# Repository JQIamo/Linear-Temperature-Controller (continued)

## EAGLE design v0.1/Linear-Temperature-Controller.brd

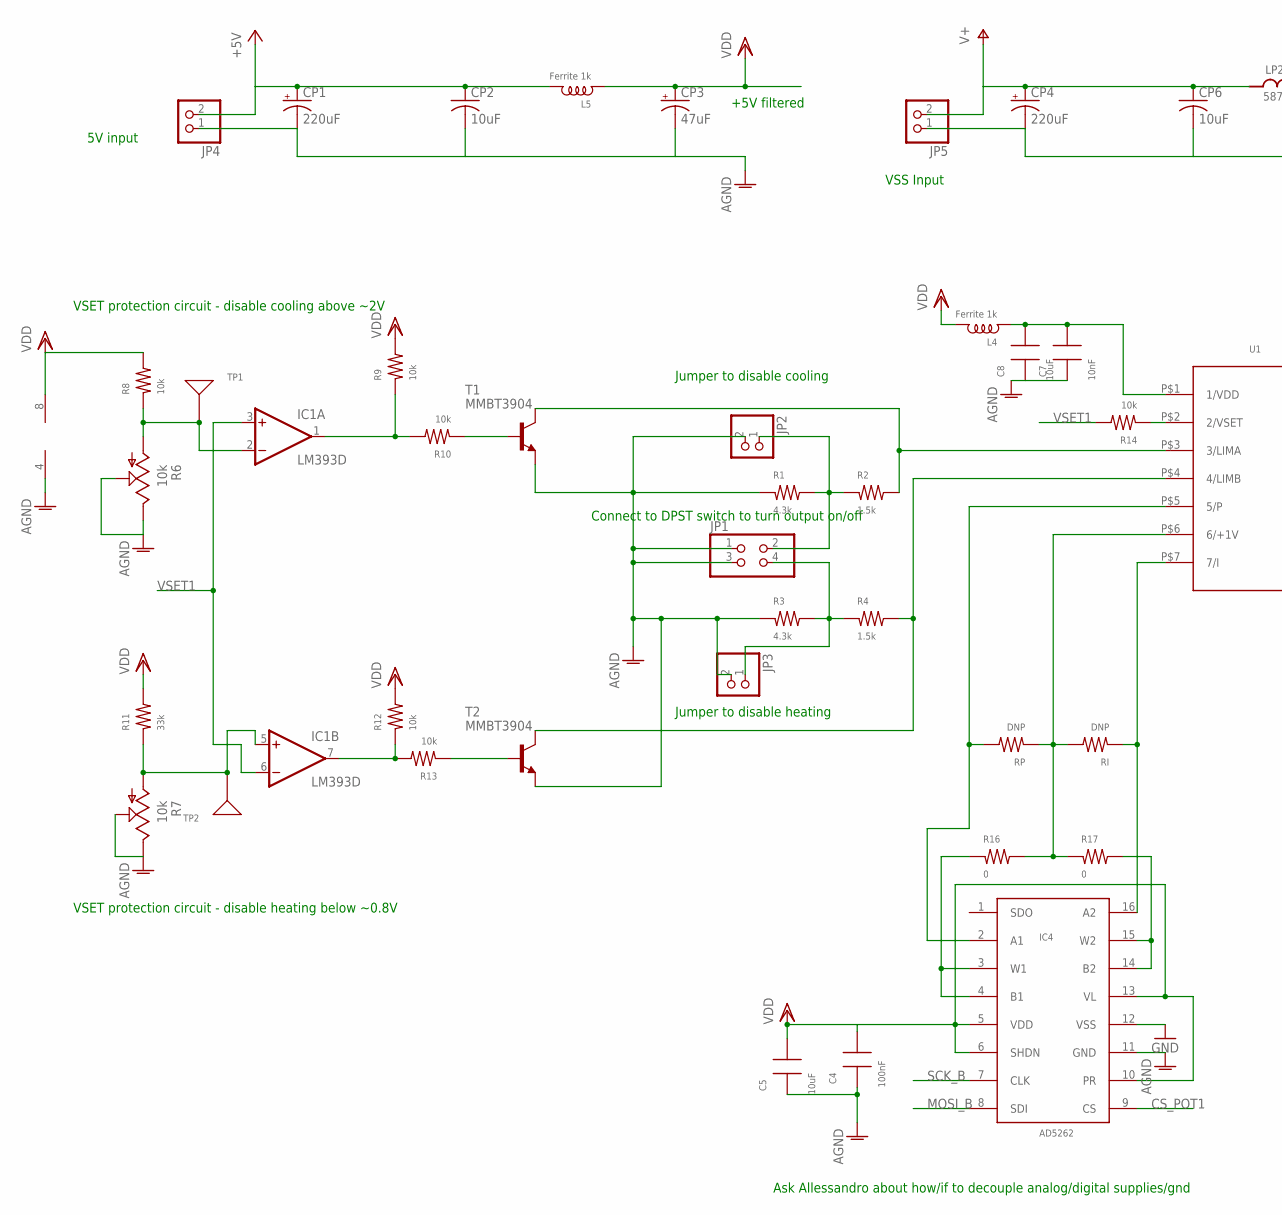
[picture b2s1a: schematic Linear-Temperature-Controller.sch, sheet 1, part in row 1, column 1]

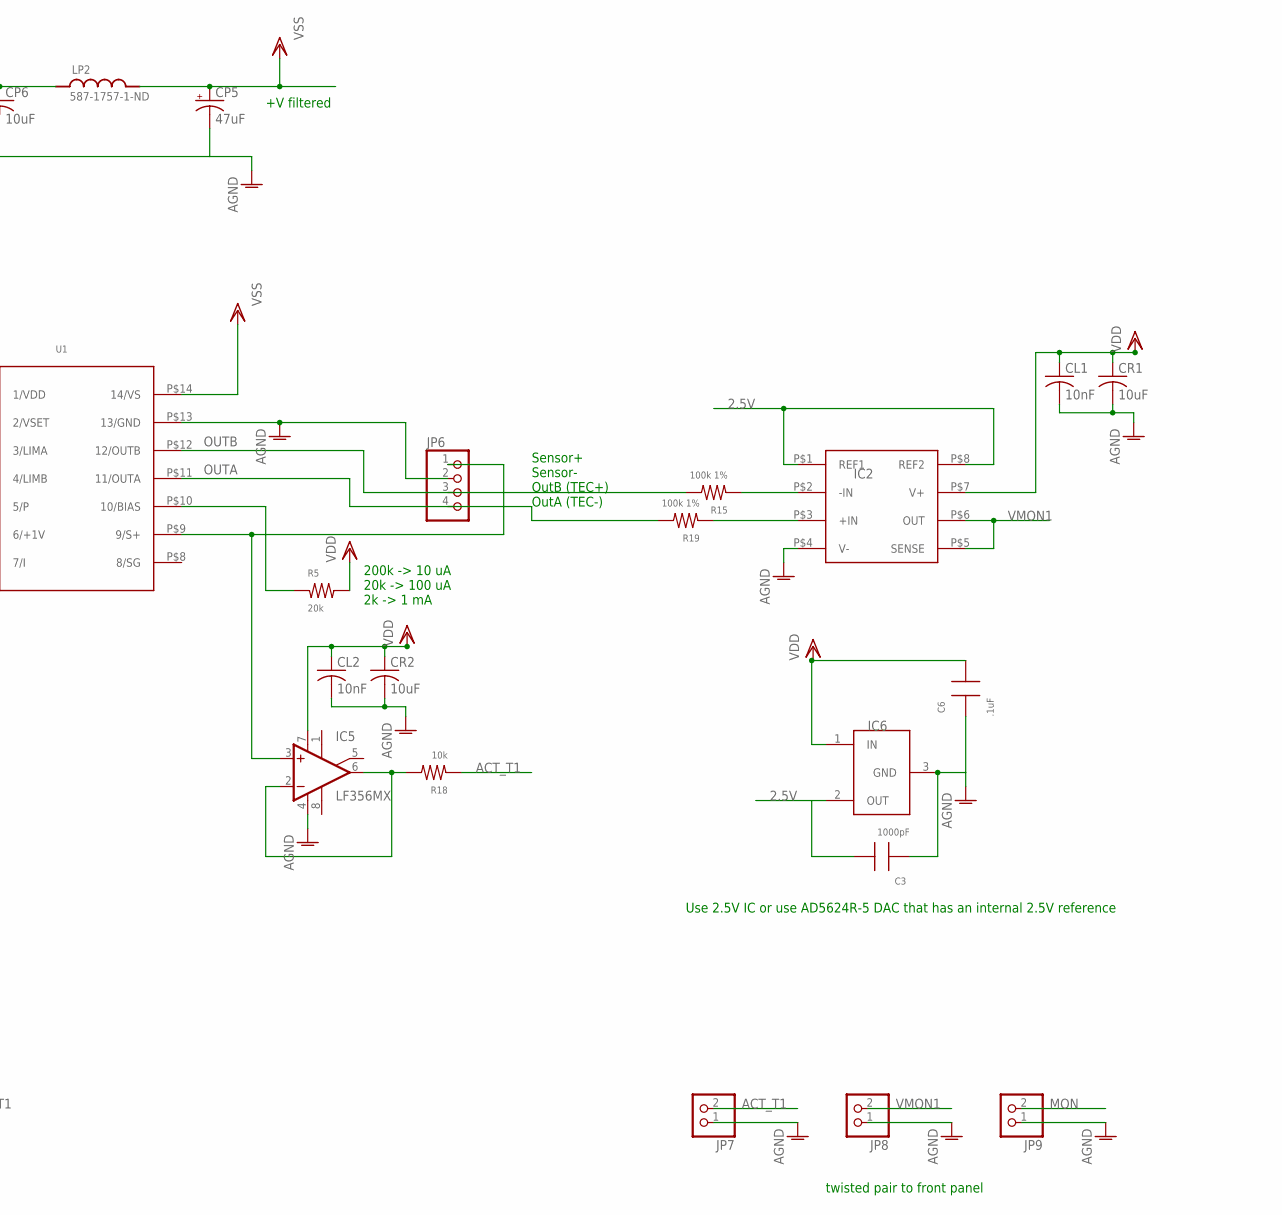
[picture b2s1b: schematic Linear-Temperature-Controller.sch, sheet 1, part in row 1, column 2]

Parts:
C3: 1000pF; 0805
C4: 100nF; 0805
C5, C8: 10uF; 0805
C6: .1uF; 0805
C7: 10nF; 0805
CL1, CL2: 10nF; C0805
CP1, CP4: 220uF; PANASONIC_F
CP2, CP6: 10uF; C0805K
CP3, CP5: 47uF; CT7343
CR1, CR2: 10uF; C0805
IC1: LM393D; SO08
IC2: INA159; VSSOP8
IC4: AD5262; TSSOP16
IC5: LF356MX; SO08
IC6: TS6001; SOT-23
JP1: PINHD-2X2; 2X02
JP2, JP3, JP4, JP5, JP7, JP8, JP9: PINHD-1X2; 1X02
JP6: PINHD-1X4; 1X04
L4, L5: Ferrite 1k; 0805
LP2: 587-1757-1-ND; L_FERRITE_1810
R1, R3: 4.3k; 0805
R2, R4: 1.5k; 0805
R5: 20k; 0805
R6, R7: 10k; 64XPOT
R8, R9, R10, R12, R13, R14, R18: 10k; 0805
R11: 33k; 0805
R15, R19: 100k 1%; 1206
R16, R17: 0; 0805
RI: DNP; 0805
RP: DNP; 0805
T1, T2: MMBT3904; SOT-23
TP1, TP2: TESTPT; 1206TESTPAD
U1: WTC3243; WTC3293

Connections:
2.5V: C3.2, IC2.P$1 (REF1), IC2.P$8 (REF2), IC6.2 (OUT); also elsewhere on the board
+5V: CP1.+, CP2.1, JP4.2, L5.2
ACT_T1: JP7.2, R18.1; also elsewhere on the board
AGND: C3.1, C4.1, C5.1, C6.1, C7.1, C8.1, CL1.2, CL2.2, CP1.-, CP2.2, CP3.-, CP4.-, CP5.-, CP6.2, CR1.2, CR2.2, IC1.4 (V-), IC2.P$4 (V-), IC4.11 (GND), IC5.4 (V-), IC6.3 (GND), JP1.1, JP1.3, JP2.2, JP3.2, JP4.1, JP5.1, JP6.2, JP7.1, JP8.1, JP9.1, R1.1, R3.1, R6.P$2 (2), R6.P$3 (3), R7.P$2 (2), R7.P$3 (3), T1.2 (E), T2.2 (E), U1.P$13 (13/GND); also elsewhere on the board
CS_POT1: IC4.9 (CS); also elsewhere on the board
DGND: IC4.12 (VSS); also elsewhere on the board
MON: JP9.2; also elsewhere on the board
MOSI_B: IC4.8 (SDI); also elsewhere on the board
unnamed: R2.2, T1.3 (C), U1.P$3 (3/LIMA)
unnamed: JP1.2, JP2.1, R1.2, R2.1
unnamed: R4.2, T2.3 (C), U1.P$4 (4/LIMB)
unnamed: JP1.4, JP3.1, R3.2, R4.1
unnamed: R5.1, U1.P$10 (10/BIAS)
unnamed: IC1.2 (-IN), R6.P$1 (1), R8.1, TP1.P$1
unnamed: IC1.5 (+IN), R7.P$1 (1), R11.1, TP2.P$1
unnamed: IC1.7 (OUT), R12.1, R13.2
unnamed: IC1.1 (OUT), R9.1, R10.2
unnamed: R10.1, T1.1 (B)
unnamed: R13.1, T2.1 (B)
unnamed: R14.1, U1.P$2 (2/VSET)
unnamed: IC5.3 (+IN), JP6.1, U1.P$9 (9/S+)
unnamed: IC2.P$2 (-IN), R15.1
unnamed: IC4.2 (A1), RP.2, U1.P$5 (5/P)
unnamed: IC2.P$3 (+IN), R19.1
unnamed: R16.2, R17.1, RI.2, RP.1, U1.P$6 (6/+1V)
unnamed: IC4.3 (W1), IC4.4 (B1), R16.1
unnamed: IC4.16 (A2), RI.1, U1.P$7 (7/I)
unnamed: IC4.14 (B2), IC4.15 (W2), R17.2
unnamed: IC5.2 (-IN), IC5.6 (OUT), R18.2
unnamed: C7.2, C8.2, L4.1, U1.P$1 (1/VDD)
OUTA: JP6.4, R19.2, U1.P$11 (11/OUTA)
OUTB: JP6.3, R15.2, U1.P$12 (12/OUTB)
SCK_B: IC4.7 (CLK); also elsewhere on the board
V+: CP4.+, CP6.1, JP5.2, LP2.P$1 (1)
VDD: C4.2, C5.2, C6.2, CL1.1, CL2.1, CP3.+, CR1.1, CR2.1, IC1.8 (V+), IC2.P$7 (V+), IC4.5 (VDD), IC4.6 (SHDN), IC4.10 (PR), IC4.13 (VL), IC5.7 (V+), IC6.1 (IN), L4.2, L5.1, R5.2, R8.2, R9.2, R11.2, R12.2; also elsewhere on the board
VMON1: IC2.P$5 (SENSE), IC2.P$6 (OUT), JP8.2; also elsewhere on the board
VSET1: IC1.3 (+IN), IC1.6 (-IN), R14.2; also elsewhere on the board
VSS: CP5.+, LP2.P$2 (2), U1.P$14 (14/VS)

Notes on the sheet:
Jumper to disable heating
Jumper to disable cooling
Connect to DPST switch to turn output on/off
200k -> 10 uA 20k -> 100 uA 2k -> 1 mA
VSET protection circuit - disable heating below ~0.8V
VSET protection circuit - disable cooling above ~2V
+5V filtered
+V filtered
5V input
VSS Input
Sensor+ Sensor- OutB (TEC+) OutA (TEC-)
Ask Allessandro about how/if to decouple analog/digital supplies/gnd
twisted pair to front panel
Use 2.5V IC or use AD5624R-5 DAC that has an internal 2.5V reference

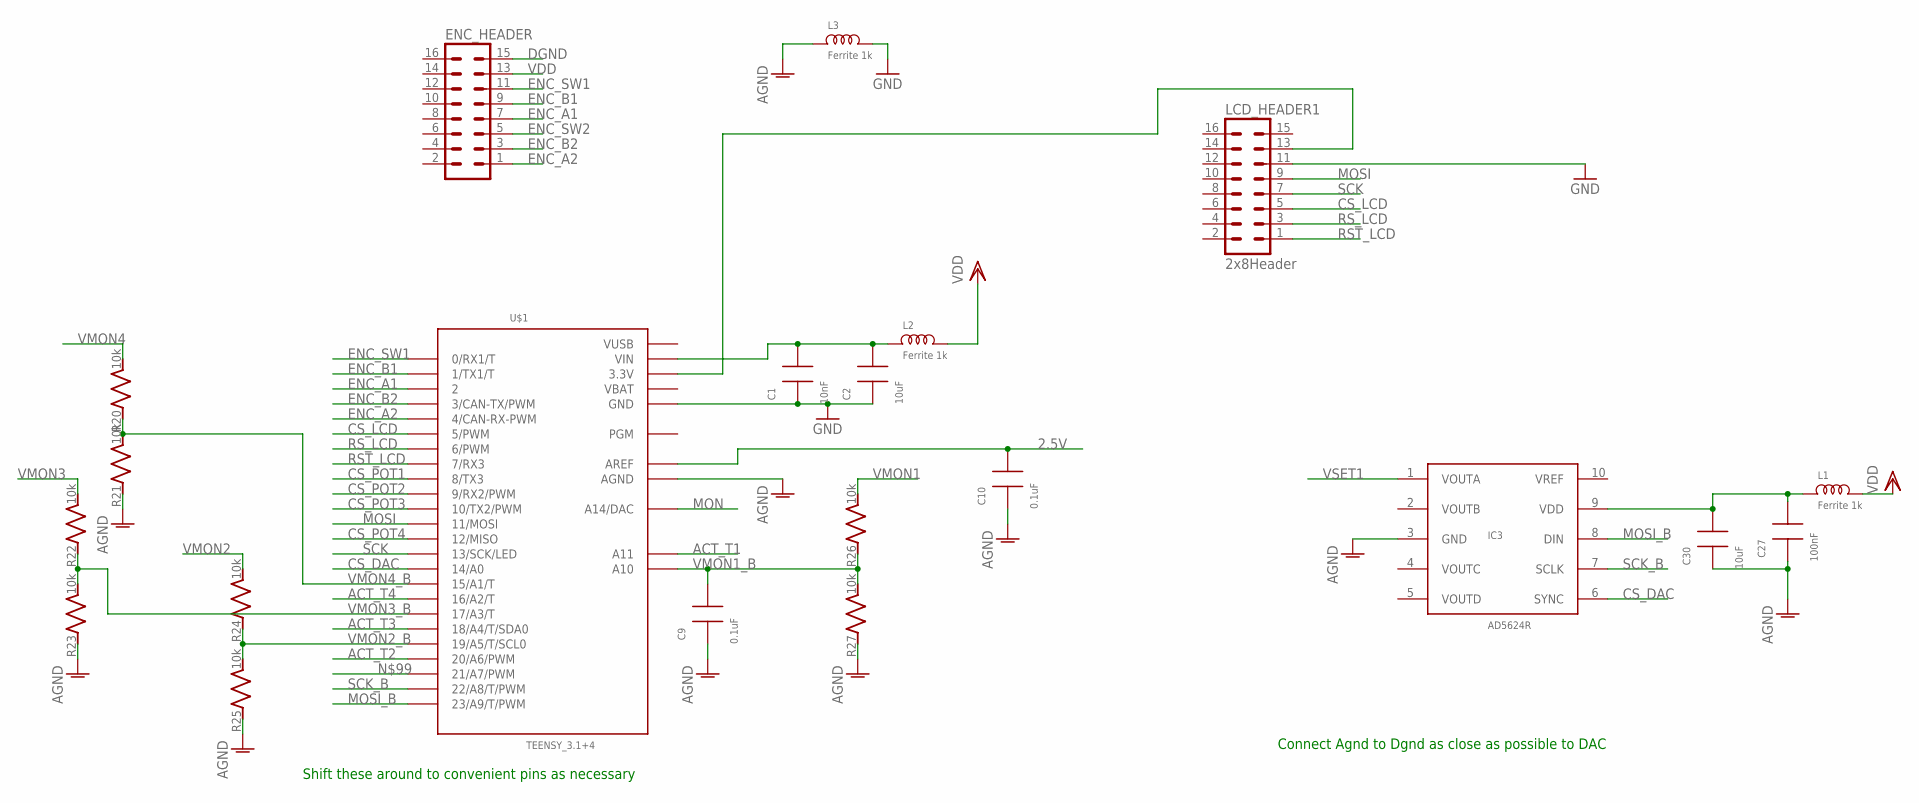
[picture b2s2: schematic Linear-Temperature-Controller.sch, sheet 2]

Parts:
C1: 10nF; 0805
C2, C30: 10uF; 0805
C9, C10: 0.1uF; 0805
C27: 100nF; 0805
ENC_HEADER: ML16
IC3: AD5624R; MSOP10
L1, L2, L3: Ferrite 1k; 0805
LCD_HEADER1: 2x8Header; ML16; PARTNO S9171-ND
R20, R21, R22, R23, R24, R25: 10k; R_0805
R26, R27: 10k; R_1206
U$1: TEENSY_3.1+4

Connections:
2.5V: C10.2, U$1.AREF; also elsewhere on the board
ACT_T1: U$1.A11; also elsewhere on the board
ACT_T2: U$1.20/A6 (20/A6/PWM)
ACT_T3: U$1.18/A4 (18/A4/T/SDA0)
ACT_T4: U$1.16/A2 (16/A2/T)
AGND: C9.1, C10.1, C27.1, C30.1, IC3.3 (GND), L3.1, R21.P$1 (1), R23.P$1 (1), R25.P$1 (1), R27.P$1 (1), U$1.AGND; also elsewhere on the board
CS_DAC: IC3.6 (SYNC), U$1.14/A0
CS_LCD: LCD_HEADER1.5, U$1.5 (5/PWM)
CS_POT1: U$1.8 (8/TX3); also elsewhere on the board
CS_POT2: U$1.9 (9/RX2/PWM)
CS_POT3: U$1.10 (10/TX2/PWM)
CS_POT4: U$1.12 (12/MISO)
DGND: C1.1, C2.1, ENC_HEADER.15, L3.2, LCD_HEADER1.11, U$1.GND, U$1.GND1 (GND); also elsewhere on the board
ENC_A1: ENC_HEADER.7, U$1.2
ENC_A2: ENC_HEADER.1, U$1.4 (4/CAN-RX-PWM)
ENC_B1: ENC_HEADER.9, U$1.1 (1/TX1/T)
ENC_B2: ENC_HEADER.3, U$1.3 (3/CAN-TX/PWM)
ENC_SW1: ENC_HEADER.11, U$1.0 (0/RX1/T)
ENC_SW2: ENC_HEADER.5
MON: U$1.A14 (A14/DAC); also elsewhere on the board
MOSI: LCD_HEADER1.9, U$1.11 (11/MOSI)
MOSI_B: IC3.8 (DIN), U$1.23/A9 (23/A9/T/PWM); also elsewhere on the board
unnamed: LCD_HEADER1.13, U$1.3.3V, U$1.3.3V1 (3.3V)
unnamed: C27.2, C30.2, IC3.9 (VDD), L1.1
unnamed: C1.2, C2.2, L2.1, U$1.VIN
RST_LCD: LCD_HEADER1.1, U$1.7 (7/RX3)
RS_LCD: LCD_HEADER1.3, U$1.6 (6/PWM)
SCK: LCD_HEADER1.7, U$1.13 (13/SCK/LED)
SCK_B: IC3.7 (SCLK), U$1.22/A8 (22/A8/T/PWM); also elsewhere on the board
VBAT: U$1.VBAT
VDD: ENC_HEADER.13, L1.2, L2.2; also elsewhere on the board
VMON1: R26.P$2 (2); also elsewhere on the board
VMON1_B: C9.2, R26.P$1 (1), R27.P$2 (2), U$1.A10
VMON2: R24.P$2 (2)
VMON2_B: R24.P$1 (1), R25.P$2 (2), U$1.19/A5 (19/A5/T/SCL0)
VMON3: R22.P$2 (2)
VMON3_B: R22.P$1 (1), R23.P$2 (2), U$1.17/A3 (17/A3/T)
VMON4: R20.P$2 (2)
VMON4_B: R20.P$1 (1), R21.P$2 (2), U$1.15/A1 (15/A1/T)
VSET1: IC3.1 (VOUTA); also elsewhere on the board
VUSB: U$1.VUSB

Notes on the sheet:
Shift these around to convenient pins as necessary
Connect Agnd to Dgnd as close as possible to DAC

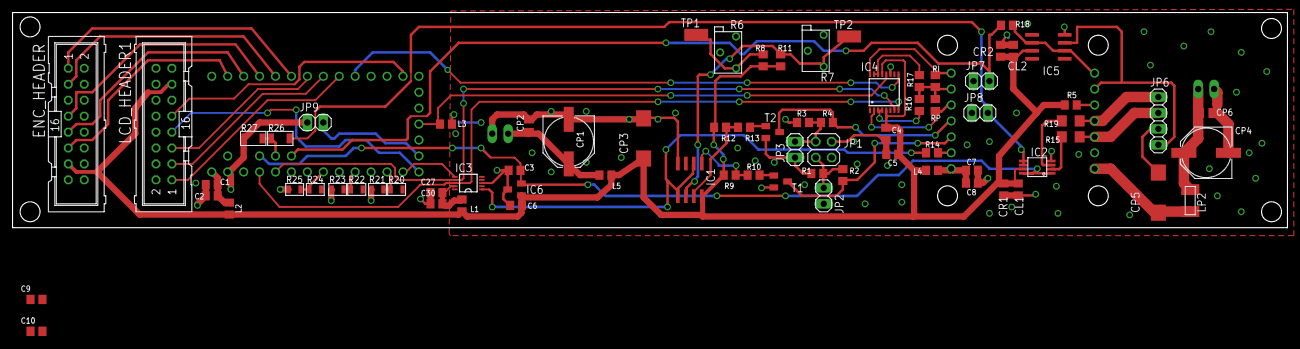
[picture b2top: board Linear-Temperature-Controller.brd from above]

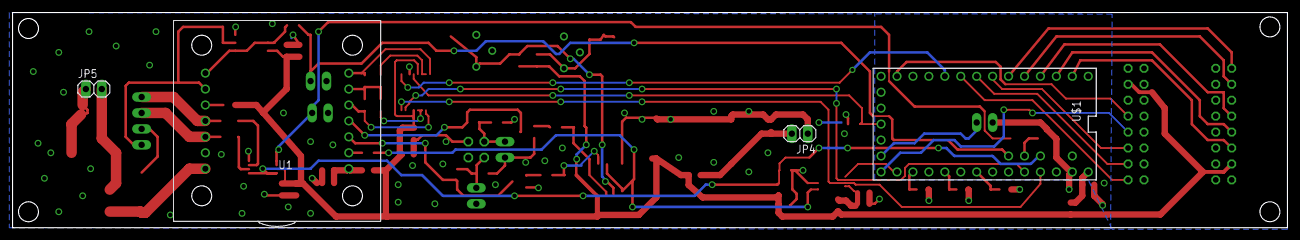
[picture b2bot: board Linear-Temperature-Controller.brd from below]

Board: 2 copper layers, 203.2 x 34.3 mm, 80 parts (4 on the bottom side), 56 nets.

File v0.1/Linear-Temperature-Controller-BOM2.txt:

Qty	Value	Device	Package	Parts	Description	DIGIKEY	PARTNO			Ordered	
1		INA159	VSSOP8	IC2	"INA159 Difference Amplifier, Texas Instruments"	296-18688-1-ND				2	
1		ML16	ML16	ENC_HEADER	HARTING					10	
7		PINHD-1X2	1X02	"JP2, JP3, JP4, JP5, JP7, JP8, JP9"	PIN HEADER						
1		PINHD-1X4	1X04	JP6	PIN HEADER						
1		PINHD-2X2	2X02	JP1	PIN HEADER						
1		TS6001	SOT-23	IC6	2.5V Reference IC	TS6001BIG325TCT-ND				2	
1		WTC3243	WTC3293	U1							
1	.1uF	CAP0805	805	C6	SMT Capacitor						
2	0	RES0805	805	"R16, R17"	SMT Resistor						
2	1.5k	RES0805	805	"R2, R4"	SMT Resistor						
1	1000pF	CAP0805	805	C3	SMT Capacitor						
2	100k 1%	RES0805	805	"R15, R19"	SMT Resistor						
2	100nF	CAP0805	805	"C4, C27"	SMT Capacitor						
2	10k	64XR	64XPOT	"R6, R7"		987-1068-ND				4	
7	10k	RES0805	805	"R9, R10, R11, R12, R13, R14, R18"	SMT Resistor						
8	10k	R_SMDR0805	R_0805	"R20, R21, R22, R23, R24, R25, R26, R27"							
2	10nF	C-USC0805	C0805	"CL1, CL2"	"CAPACITOR, American symbol"						
2	10nF	CAP0805	805	"C1, C7"	SMT Capacitor						
2	10uF	C-USC0805	C0805	"CR1, CR2"	"CAPACITOR, American symbol"						
2	10uF	C-USC0805K	C0805K	"CP2, CP6"	"CAPACITOR, American symbol"						
4	10uF	CAP0805	805	"C2, C5, C8, C30"	SMT Capacitor						
1	20k	RES0805	805	R5	SMT Resistor						
2	220uF	CPOL-USF	PANASONIC_F	"CP1, CP4"	"POLARIZED CAPACITOR, American symbol"	PCE3955CT-ND				4	
1	2x8Header	ML16	ML16	LCD_HEADER1	HARTING		S9171-ND			see above	
2	3.5k	RES0805	805	"R1, R3"	SMT Resistor						
1	35k	RES0805	805	R8	SMT Resistor						
2	47uF	CPOL-USCT7343	CT7343	"CP3, CP5"	"POLARIZED CAPACITOR, American symbol"	495-1571-1-ND				4	
1	587-1757-1-ND	L_FERRITE_SMD	L_FERRITE_1810	LP2		587-1757-1-ND				2	
1	AD5262	AD5262	TSSOP16	IC4	AD5262 dual circuit digital pot	AD5262BRUZ200-ND				2	
1	AD5624R	AD5624R	MSOP10	IC3	AD5624R Quad Output DAC w/internal Vref	AD5624RBRMZ-3-ND				2	
2	DNP	RES0805	805	"RI, RP"	SMT Resistor						
5	Ferrite 1k	INDUCTOR-0805	805	"L1, L2, L3, L4, L5"	SMT Inductor.	445-5223-1-ND				10	
1	LM393D	LM393D	SO08	IC1	COMPARATOR	296-1015-5-ND					
2	MMBT3904	MMBT3904	SOT-23	"T1, T2"	NPN TRANSISTOR	MMBT3904-FDICT-ND				4	
1	OP27	OPAMP-SO	SO08	IC5	"Basic Op Amp. Be sure to check actual pinout of your device, and"						
1	TEENSY_3.1+4	TEENSY_3.1+4	TEENSY_3.1+4	U$1	"Footprint for Teensy 3.1 board using all through-holes, i.e. the entire perimeter plus the 4 through-holes inboard (A10,A11,AREF, VUSB)"						
2	TEST_PAD150	TEST_PAD150	TESTPAD	"TP1, TP2"	1206 test pad	A106143CT-ND				20	
					Power supply	CDPM1000-ND				1	
											
	Not ordered					490-9741-1-ND				50	"1000pF, 50V, 10% 0805 Cer Cap"
						490-5523-1-ND				50	"10uF, 25V 10% 0805 Cer Cap"
						490-1664-1-ND				50	"10000pF, 50V, 10% Cer Cap"

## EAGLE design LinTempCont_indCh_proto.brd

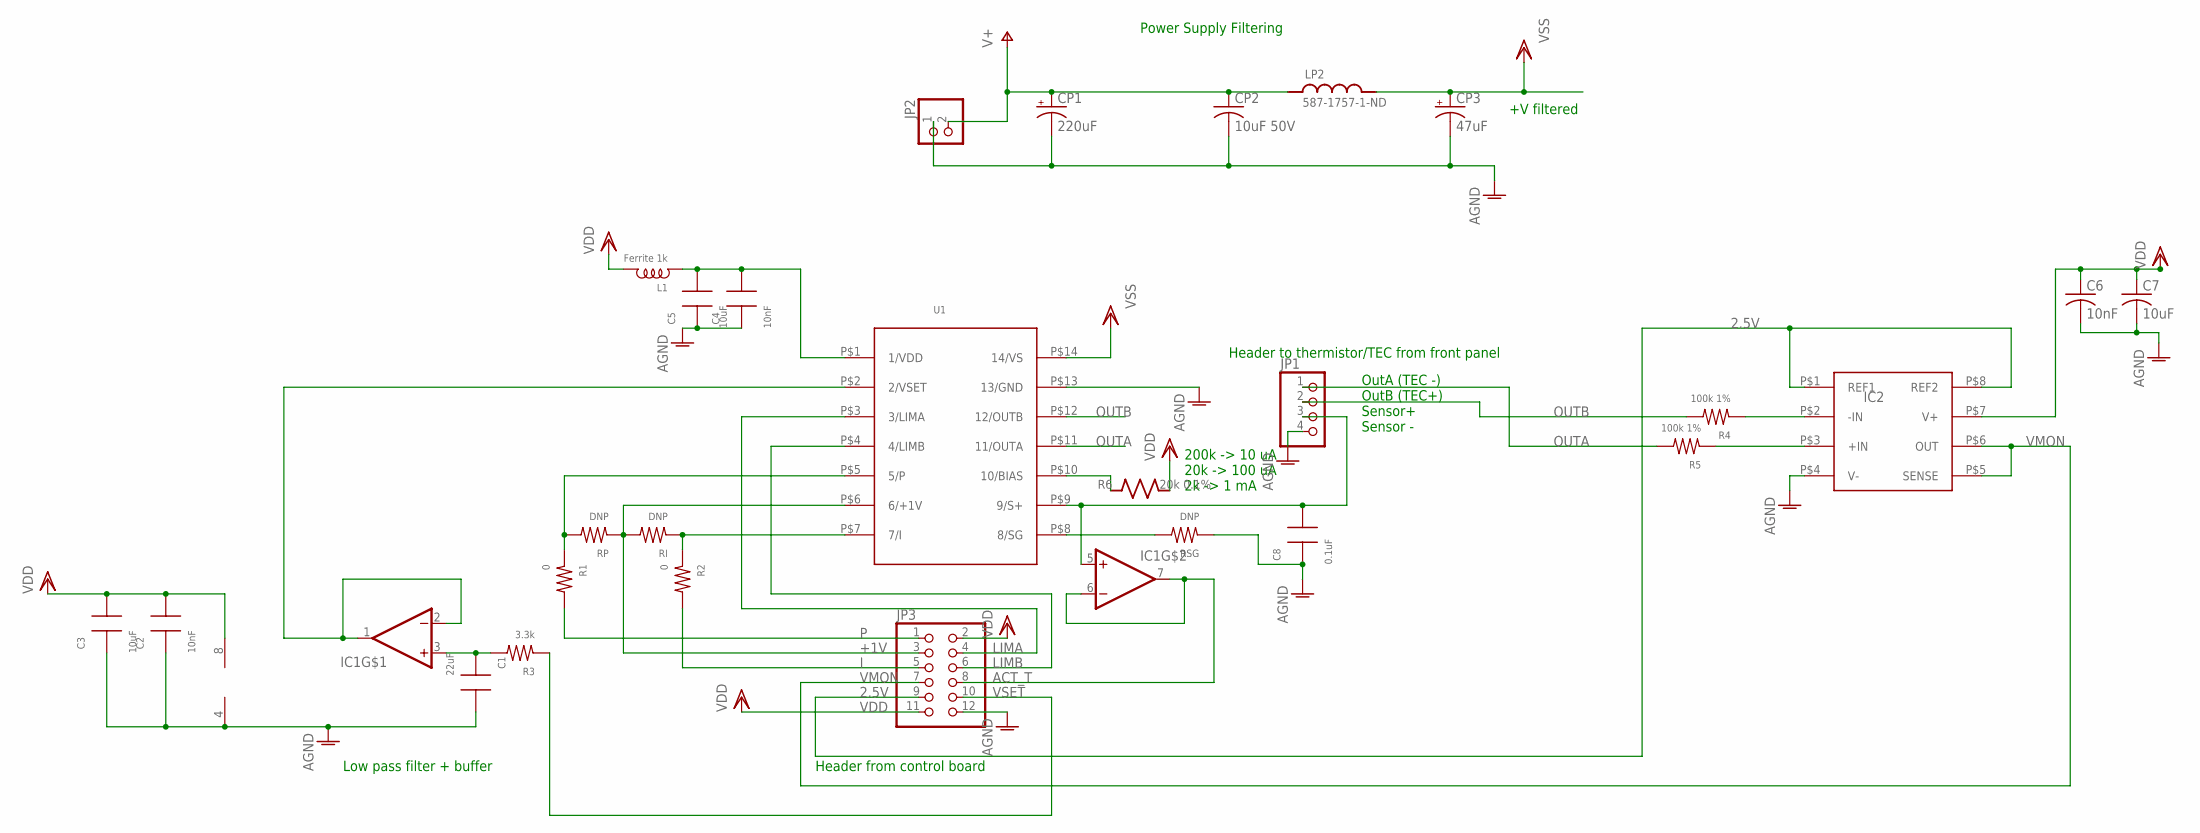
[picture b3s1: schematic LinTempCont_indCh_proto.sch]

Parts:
C1: 22uF; 0805
C2: 10nF; 0603
C3: 10uF; 0805
C4: 10nF; 0805
C5: 10uF; 0603
C6: 10nF; C0603
C7: 10uF; C0805
C8: 0.1uF; 0603
CP1: 220uF; PANASONIC_F
CP2: 10uF 50V; C1206
CP3: 47uF; CT7343
IC1: OP727; TSSOP8
IC2: INA159; VSSOP8
JP1: SCRWTRM-1X4/90_ED550; 1X04_RA_SCRWTRM_ED550
JP2: SCRWTRM-1X2/90_ED550; 1X02_RA_SCRWTRM_ED550
JP3: PINHD-2X6; 2X06
L1: Ferrite 1k; 0805
LP2: 587-1757-1-ND; L_FERRITE_1810
R1, R2: 0; 0603
R3: 3.3k; 0603
R4, R5: 100k 1%; 0603
R6: 20k 0.1%; R_0805
RI: DNP; 0603
RP: DNP; 0603
RSG: DNP; 0603
U1: WTC3243; WTC3293

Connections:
2.5V: IC2.P$1 (REF1), IC2.P$8 (REF2), JP3.9
+1V: JP3.3, RI.2, RP.1, U1.P$6 (6/+1V)
ACT_T: IC1.6 (-IN), IC1.7 (OUT), JP3.8
AGND: C1.2, C2.1, C3.1, C4.1, C5.1, C6.2, C7.2, C8.1, CP1.-, CP2.2, CP3.-, IC1.4 (V-), IC2.P$4 (V-), JP1.4, JP2.1, JP3.12, RSG.1, U1.P$13 (13/GND)
I: JP3.5, R2.2
LIMA: JP3.4, U1.P$3 (3/LIMA)
LIMB: JP3.6, U1.P$4 (4/LIMB)
unnamed: R1.1, RP.2, U1.P$5 (5/P)
unnamed: C8.2, IC1.5 (+IN), JP1.3, U1.P$9 (9/S+)
unnamed: R2.1, RI.1, U1.P$7 (7/I)
unnamed: R6.P$1 (1), U1.P$10 (10/BIAS)
unnamed: C1.1, IC1.3 (+IN), R3.2
unnamed: RSG.2, U1.P$8 (8/SG)
unnamed: IC1.1 (OUT), IC1.2 (-IN), U1.P$2 (2/VSET)
unnamed: IC2.P$2 (-IN), R4.1
unnamed: IC2.P$3 (+IN), R5.1
unnamed: C4.2, C5.2, L1.1, U1.P$1 (1/VDD)
OUTA: JP1.1, R5.2, U1.P$11 (11/OUTA)
OUTB: JP1.2, R4.2, U1.P$12 (12/OUTB)
P: JP3.1, R1.2
V+: CP1.+, CP2.1, JP2.2, LP2.P$1 (1)
VDD: C2.2, C3.2, C6.1, C7.1, IC1.8 (V+), IC2.P$7 (V+), JP3.2, JP3.11, L1.2, R6.P$2 (2)
VMON: IC2.P$5 (SENSE), IC2.P$6 (OUT), JP3.7
VSET: JP3.10, R3.1
VSS: CP3.+, LP2.P$2 (2), U1.P$14 (14/VS)

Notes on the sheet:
Header from control board
Power Supply Filtering
Header to thermistor/TEC from front panel
+V filtered
200k -> 10 uA 20k -> 100 uA 2k -> 1 mA
Low pass filter + buffer
OutA (TEC -) OutB (TEC+) Sensor+ Sensor -

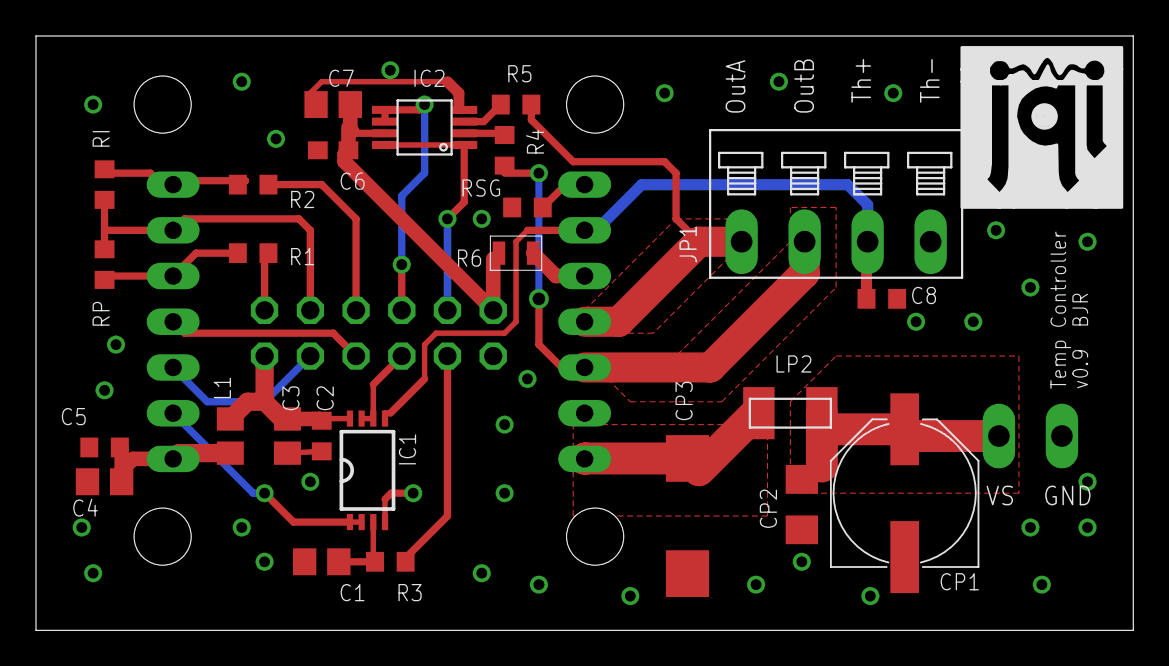
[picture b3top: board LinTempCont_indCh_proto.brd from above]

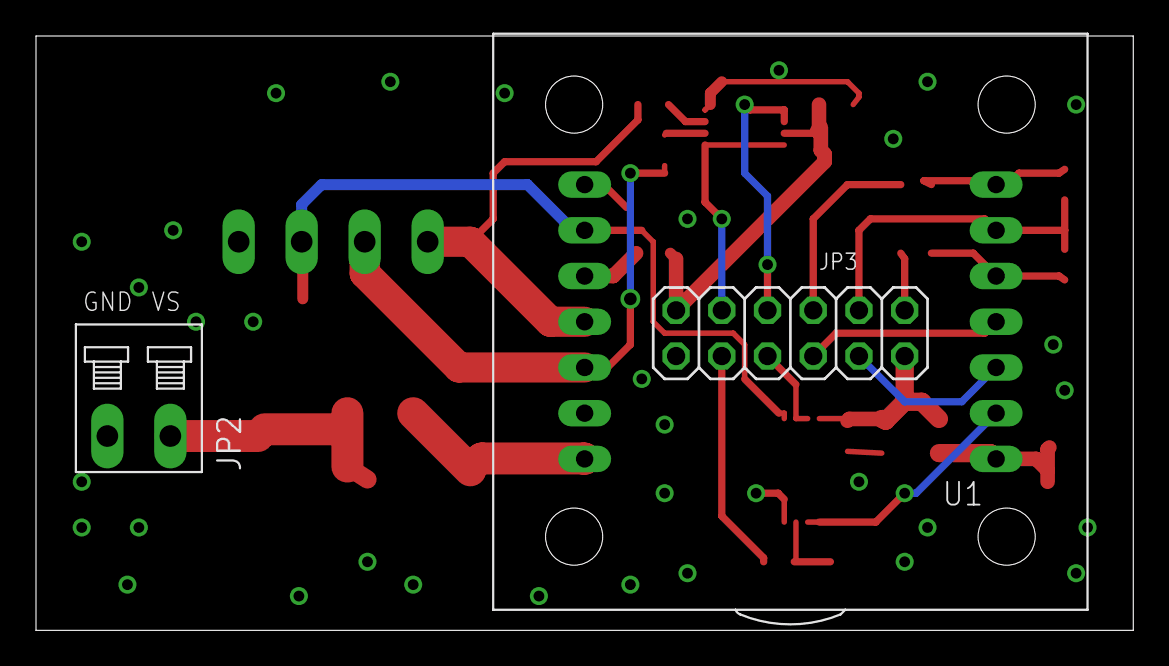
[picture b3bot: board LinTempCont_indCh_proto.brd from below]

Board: 2 copper layers, 61.0 x 33.0 mm, 29 parts (3 on the bottom side), 25 nets.

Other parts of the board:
U$1: JQI_LOGO_NEGATIVE-SILKSCREEN

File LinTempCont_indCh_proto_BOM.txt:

"Qty";"Value";"Device";"Package";"Parts";"Description";"DIGIKEY";"MFR_PN";
"1";"";"INA159";"VSSOP8";"IC2";"INA159 Difference Amplifier, Texas Instruments";"296-18688-1-ND";"";
"1";"";"OP727";"TSSOP8";"IC1";"OP727 Dual Op Amp";"OP727ARUZ-ND";"";
"1";"";"PINHD-2X6";"2X06";"JP3";"PIN HEADER";"";"";
"1";"";"SCRWTRM-1X2/90";"1X02_RA_SCRWTRM";"JP2";"Screw Terminal";"ED2623-ND";"OSTTF020161";
"1";"";"SCRWTRM-1X4/90";"1X04_RA_SCRWTRM";"JP1";"Screw Terminal";"ED2625-ND";"OSTTF040161";
"1";"";"WTC3243";"WTC3293";"U1";"WTC3243 linear temp controller chip from Team Wavelength";"";"";
"2";"0";"RES0603";"0603";"R1, R2";"SMT Resistor";"";"";
"1";"0.1uF";"CAP0603";"0603";"C8";"SMT Capacitor";"";"";
"2";"100k 1%";"RES0603";"0603";"R4, R5";"SMT Resistor";"";"";
"1";"10nF";"C-USC0603";"C0603";"C6";"CAPACITOR, American symbol";"";"";
"2";"10nF";"CAP0603";"0603";"C2, C4";"SMT Capacitor";"";"";
"1";"10uF";"C-USC0603";"C0603";"C7";"CAPACITOR, American symbol";"";"";
"1";"10uF";"C-USC0805K";"C0805K";"CP2";"CAPACITOR, American symbol";"";"";
"2";"10uF";"CAP0603";"0603";"C3, C5";"SMT Capacitor";"";"";
"1";"20k 0.1%";"R_SMDR0805";"R_0805";"R6";"";"";"";
"1";"220uF";"CPOL-USF";"PANASONIC_F";"CP1";"POLARIZED CAPACITOR, American symbol";"";"";
"1";"22uF";"CAP0805";"0805";"C1";"SMT Capacitor";"";"";
"1";"3.3k";"RES0603";"0603";"R3";"SMT Resistor";"";"";
"1";"47uF";"CPOL-USCT7343";"CT7343";"CP3";"POLARIZED CAPACITOR, American symbol";"";"";
"1";"587-1757-1-ND";"L_FERRITE_SMD";"L_FERRITE_1810";"LP2";"";"";"";
"3";"DNP";"RES0603";"0603";"RI, RP, RSG";"SMT Resistor";"";"";
"1";"Ferrite 1k";"INDUCTOR-0805";"0805";"L4";"SMT Inductor.";"";"";

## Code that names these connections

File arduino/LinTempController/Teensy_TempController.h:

/*
   Teensy_TempController.h  - Pin mappings for the Teensy_TempController
   
   Created by Neal Pisenti, 2015, modified by Ben Reschovsky
   JQI - Joint Quantum Institute

   This program is free software: you can redistribute it and/or modify
   it under the terms of the GNU General Public License as published by
   the Free Software Foundation, either version 3 of the License, or
   (at your option) any later version.

   This program is distributed in the hope that it will be useful,
   but WITHOUT ANY WARRANTY; without even the implied warranty of
   MERCHANTABILITY or FITNESS FOR A PARTICULAR PURPOSE.  See the
   GNU General Public License for more details.

   You should have received a copy of the GNU General Public License
   along with this program.  If not, see <http://www.gnu.org/licenses/>.

*/

/*!	\file	Teensy_TempController.h
 *	\brief	Pin mappings for Teensy_TempController PCB.
 *	\details Define statements for pin mappings on Teensy frequency shield.
 *          See https://github.com/JQIamo/mcu-accessories for the breakout
 *          shield, and https://www.pjrc.com/teensy/teensy31.html for info
 *			on the Teensy dev board.
 *
 *	\author	Ben Reschovsky <breschov@umd.edu>
 *  \version 0.1
 *	\date	2015-06-08
 */


/*! \name Pins for analog monitor
 *
 */
//! @{

#define VMON4 		A1
#define ACT_T4		A2

#define VMON3 		A3
#define ACT_T3		A4

#define VMON2 		A5
#define ACT_T2		A6

#define VMON1 		A10
#define ACT_T1		A11

//Are these needed: MON_OUT (A14/DAC), 2.5 Voltage ref (AREF), 
#define ANALOG_OUT_PIN    A14

//! @}

/*! \name Pins for digital potentionmeters and DAC:
 *
 */
//! @{
#define CS_POT1			8
#define CS_POT2			9
#define CS_POT3			10
#define CS_POT4			12
#define CS_DAC			14


//!@}

/*! \name Pins for LCD & Switches/encoders
 *
 */
//! @{

#define RST_LCD			7
#define RS_LCD			6
#define CS_LCD			5

#define ENC_A1			2
#define ENC_B1			1
#define ENC_SW1			0

#define ENC_B2			3
#define ENC_A2			4
#define ENC_SW2                 21

//! @}

/*! \name Pins for SPI 
 *
 */
//! @{

//#define MOSI		11
//#define SCK			13
#define SCK_B			22
#define MOSI_B			23

//! @}

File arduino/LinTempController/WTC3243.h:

/*
   WTC3243.h  - Library for controlling a WTC3243 linear temperature controller from Team Wavelength
   
   Created by Ben Reschovsky, 2015
   JQI - Joint Quantum Institute

   This program is free software: you can redistribute it and/or modify
   it under the terms of the GNU General Public License as published by
   the Free Software Foundation, either version 3 of the License, or
   (at your option) any later version.

   This program is distributed in the hope that it will be useful,
   but WITHOUT ANY WARRANTY; without even the implied warranty of
   MERCHANTABILITY or FITNESS FOR A PARTICULAR PURPOSE.  See the
   GNU General Public License for more details.

   You should have received a copy of the GNU General Public License
   along with this program.  If not, see <http://www.gnu.org/licenses/>.

*/

/*!	\\file	WTC3242.h
 *	\\brief	Library for controlling WTC3243 temperature controller
 *	\\details  Depends on AD5262 to control P
 *          See http://www.teamwavelength.com/downloads/datasheets/wtc3243.pdf#page=1 for datasheet. 
 *
 *	\\author	Ben Reschovsky <breschov@umd.edu>
 *  \\version 0.1
 *	\\date	2015-06-10
 */

#ifndef WTC3243_h
#define WTC3243_h

#include "Arduino.h"
#include "AD5262.h"
#include "AD56X4R.h"

class WTC3243
{
	public:
		//Constructor function
		//Do I need the DAC_CS pin here or can I use a global variable?
		WTC3243(byte CS_POT, byte SCK_PIN, byte MOSI_PIN, byte CS_DAC_PIN , byte DAC_Ch, byte VMON, byte ACT_T, unsigned long R_MIN, unsigned long R_MAX);

		void init(double _BIAS_CURRENT, double _STEINHART_A, double _STEINHART_B, double _STEINHART_C, float _MIN_TEMP, float _MAX_TEMP);


		//other variables needed for calibration:
		// max/min resistance of pot: _R_MIN, _R_MAX;
		// max/min allowed value of P, I: _P_MAX, _P_MIN, _Itc_Max, _Itc_Min (global?)
		//actual value of 2.5 voltage reference: VREF	(global)
		//bits used for analog read: ANALOG_READ_BITS	(global)
		//bias current	
		//steinhard coefficients
		//min temp
		//max temp
		//Dac reference voltage (global)

		//Set the proportional gain in (A/V)
		void setP(byte);

		//Set the integrator time constant (in sec)
		void setI(float);

		//Read current prop gain
		byte getP();

		//read current integrator time constant 
		float getI();

		//Set desired temperature voltage
		void setTempV(double V, AD56X4R& dac);

		//Set desired temperature
		void setTemp(double temp, AD56X4R& dac);

                //Read voltage at specified analog input pin
                float readVoltage(byte analogPin);

		//Get the measured temperature
		float getActTemp();

                //Get the voltage across the TEC/heater
                float getOutputVoltage();

		//Get the temperature set point
		float getTempSetPt();

		//Get the temperature set voltage();
		double getTempSetV();

		//Get the error signal (act - set temp)
		float getTempDev();

                //Set the minimum temperature
                void setMinTemp(float minTemp);
                
                //Set the maximum temperature
                void setMaxTemp(float maxTemp);
                
                //Get the minimum temperature
                float getMinTemp();
                
                //Get the maximum temperature
                float getMaxTemp();
                
                //Instance digipot object
		AD5262 _dPOT;

                //Instance DAC object
                //AD56X4R* _dac;

	private:
		//Instance variables that hold pin mappings
		byte _CS_POT, _SCK_PIN, _MOSI_PIN, _CS_DAC, _VMON_PIN, _ACT_T_PIN;

		//Instance variables used for DAC communication
		byte _DAC_CH;

		//Instance variables used to calibrate the max/min resistance of the digit:
		unsigned long _R_MIN, _R_MAX;

		//Instance variables that store the current proportional and integral settings:
		byte _Pgain, _P_MAX, _P_MIN;
		float _Itc, _Itc_MAX, _Itc_MIN;

		//Instance variables used to store the temperature set voltage:
		double _setV;

		//Instance variables used to calibrate the voltage across the thermistor to a temperature
		double _BIAS_CURRENT, _STEINHART_A, _STEINHART_B, _STEINHART_C;

		//Instance variables used to store the set, actual, min/max temperatures:
		float _actT, _setT, _min_temp, _max_temp, _tempDev;

};

#endif

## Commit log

2015-05-14 :confetti_ball: Added .gitattributes & .gitignore files
2015-05-14 Started Eagle Schematic
2015-05-15 Added current limit portion
2015-05-18 Add input voltage protection
2015-05-18 Update .gitignore file
2015-05-19 Schematic Progress
    Include microcontroller, DAC, digital POT and more
2015-05-20 Replace microcontroller with Teensy
2015-05-21 Add differential amplifier, separate AGND from DGND
2015-05-25 Schematic progress
    Add 2.5V ref, swap trimpot package, add monitor headers
2015-05-26 Start laying out board and update schematic
2015-05-26 Progress...
    Added voltage divider to Teensy analog inputs, added a couple extra
    teensy channels, layout progress
2015-05-26 Add BOM
2015-05-28 Update BOM, continue laying out board
    Also add a new board file to play around with having a bus of traces for
    eventually extending the circuit to 4 channels
2015-05-28 Finished first attempt at board layout
2015-05-28 Update .gitignore
    Now includes the bus-layout .brd and .sch files, which were a failed
    experiment.
2015-06-01 Clearance increased and added few vias
2015-06-09 Start arduino code
    Add header to define Teensy pins. Started writing functions to write to
    the digipot and DAC. These should eventually be moved to their own
    library.
2015-06-10 Added additional libraries
    Copied over Encoder, LCD, Menu libraries from Neal A's AOM driver
    project, added AD5262 library
2015-06-11 AD5262 library fixes, added analog read functions
2015-06-12 Incorporate and modify LCD, Encoder, Menu classes
    Copied updated LCD, Encoder, and Menu classes from Neal Anderson's AOM
    driver software. Started modifying them for my purposes, including bug
    fixes and having the encoder value tracked as a double instead of
    integer.
2015-06-22 Create WTC3243 Library
    Add a WTC3243 class to handle functions like setTemp, readTemp,
    setPropGain, setIntTimeConstant. Also added a header file to store
    settings common to the entire board.
2015-06-22 Add DAC library, start incorporating it into WTC3243 library
2015-06-23 Added a few more details for encoder implementation
2015-06-23 Version 0.1
    First fully working sketch. This version incorporates four menu modes
    (set temp, set prop gain, set int time constant, monitor voltage).
    Things that still need to get added besides the obvious real world
    testing:
    -Read/Write settings to EEPROM
    -Possibly control upper/lower temp limit on front panel
2015-06-28 Add read/write to EEPROM
    Temp Set Pt, Pgain, Itc are now saved to memory when the encoder button
    is held. (It is easy to change this to save every hour instead). This
    commit needs testing.
2015-06-29 Fix minor errors on prototype schematic
2015-06-30 Finish implementing save settings, minor code fixes
2015-07-01 Start 4-Ch prototype schematic
    Add teensy, DAC, voltage ref, and 1 channel. Still to do: copy/paste for
    3 other channels, add rotary encoders.
2015-07-03 Main board progress, started individual channel boards
2015-07-07 Schematic updates and progress routing both boards
2015-07-08 Finished routing board
    Still to do: review layout, add vias, clean up silkscreen
2015-07-09 Board/Schematic updates and tweaks
    Incorporate suggestions from Neal and Alessandro
2015-07-10 Board/Schematic Clean up-lcd.init tweak
    Added encoder hold event to initialize LCD to try to get around bug
    where LCD display goes blank. The bug appears to be from a loose solder
    connection on first prototype
2015-07-13 Add DAC Vref Jumper/Silkscreen Cleanup
2015-07-15 Add BOM, minor updates to reflect part availability
2015-07-15 Prepare for ordering boards
    Update BOM, minor changes to board to move header slightly, ensure
    silkscreen is using vector fonts
2015-07-17 Generate Gerber Files, clean up folders
2015-07-22 Add ability to change min/max temp from front panel
2015-07-22 Add code for 4 channels
    Still to do: handle saving and reading of settings from EEPROM
2015-07-23 Add read/write to EEPROM for 4 ch
2015-07-24 Code cleanup & add flag for first save
2015-07-30 Add PinMapping namespace
    This commit is untested but it compiles, which means it should work.
2015-07-31 Add ability to measure max/min digipot resistances
    Untested!
2015-08-05 Start eagle files for ind. ch. V1.0 boards
    Swapped values of C4 and C5 so that the 10 uF capacitor has the 0805
    footprint and the 10 nF cap has the 0603 footprint
2015-08-27 Update pin mappings for new board
2015-08-27 Small fix to correctly print version num to serial
2015-08-27 Modify LCD.cpp
    Add lines to ensure chip select line is set as an output pin. This
    should only be necessary when the DIN (MISO) line (pin 12 for the
    teensy) is used a the chip select. Also changed how the settings are
    initialized to allow the communication speed to be changed.
2015-09-03 Modify AD56X4R library: voltage offset & vref flag
    Add a calibration constant to include a small voltage offset in the DAC
    transfer function. Also include a flag to indicate if the DAC's voltage
    reference is external or internal
2015-09-03 Calibrate settings for 4-ch prototype
    Also add voltage offset and DAC vref flag
2015-09-03 Fix calibration menu, update encoder button_pressed()
2015-09-03 Fixed a couple small errors found on prototype
    R1/R2, R37/R38, R73/R74 had the locations of their silkscreen labels
    swapped. Also changed value of C10 from 0.1uF to 1nF to avoid
    oscillations of voltage reference
2015-09-03 Started version 1.1
    Replaced 2 pin jumper to switch between internal/external DAC VREF with
    a 4 pin jumper to allow placement of a 100 nF capacitor between DAC Vref
    and gnd (when internally referenced)
2015-09-03 Minor change to trace thickness
2015-09-09 Add simple sketch for temp monitoring
    Uses a second teensy to log the temperature out of the control loop. Use
    a program like coolterm to monitor the values read and printed to the
    serial command line.
2015-10-14 Finish version 1
    Reorganize file structure. Package version 1 files nicely along with BOM
    in order to get boards assembled
2015-10-15 Add centroid files for assembly
2016-01-06 Add separate .h files for each version of the board (which require different calibrations)
2016-01-08 Update AD56X4R library to take an array of offset voltages (one per each of the four channels)
2016-01-15 Calibration updates
2016-08-22 Update version 2 calibration file
    dac_offset should now be an array of floats instead of a single float
2016-08-22 Add ability to print temperatures to serial line for monitoring
2016-08-22 Change format of serial port monitoring
    Replace two spaces with a tab
2016-09-09 Include EEPROMex Library in arduino folder
    If the EEPROMex library is run in debug mode, then you are limited to
    100 writes to memory, which causes problems by not saving your settings.
    This commit includes the EEPROMex files in the arduino folder so a new
    user doesn't have to remember to comment out the "define
    _EEPROMEX_DEBUG" statement in EEPROMex.cpp.
    Also, comment out the lines that print changes to the DAC setpoint to
2017-09-27 Add front panel design file
